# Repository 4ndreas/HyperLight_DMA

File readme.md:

# Hyperlight LED Driver
STM32F407 based WS2811/12 Led driver with 16-channel DMA output

## variant 
* added custom variant with DMA interrupt function

## patched libraies are
* Artnet
* Ethernet
	* Changed SPI speed
	* Port so 2 with increases the buffer in the W5500 chip per port to 8k
* Adafruit_SSD1306
	* Display size to 128x64
	
* Overrides for ST SPI Hal Code beed as compile options: -include "<absolute-src-path>/make_weak.h"

## ToDo

* Improvement for
    * better bit sorting
    * setLED function
    * setSnakeLED
    * better solution for other color modes

* Webserver Config for
    * Color Mode
    * offset 
    * Snake Wireing
    * FPS Counter

* USB test
* SD-Card 
* better Webserver with SD card or the website.h methode
* DMX out

## How to Install

```
https://github.com/stm32duino/BoardManagerFiles/raw/master/STM32/package_stm_index.json
```

![alt text][preferences1]
![alt text][preferences2]

### Adding a new board variant 

Path to the boards:

coppy the variants\Hyperlight folder in the package dir:

```
\Sloeber\arduinoPlugin\packages\STM32\hardware\stm32\1.7.0\variants\Hyperlight
```
or if the plain arduino IDE is used in  
```
.user\AppData\Local\Arduino15\packages\STM32\hardware\stm32\1.7.0\variants
```

Setting for the board:

Optimize: "Smallest(-Os default)"

![alt text][properties]

Add make_weak to "compiler Options"
```
-include "C:\Users\ahoel\Documents\sloeber-workspace\hyperlight_dma\make_weak.h"
```
![alt text][properties2]

### How to Debug
See the wiki form the STM32 Core
https://github.com/stm32duino/wiki/wiki/How-to-debug

Download sloeber-IDE form 
http://eclipse.baeyens.it/index.shtml

Change Target to:
```
-s "${openocd_path}/../scripts" -f interface/stlink-v2-1.cfg -f target/stm32f4x.cfg
```
![alt text][debug1]
![alt text][debug2]

[preferences1]: img/preferences_1.JPG "Settings URL for STM32Core"
[preferences2]: img/preferences_2.JPG "Settings URL for STM32Core"
[properties]: img/properties.JPG "properties of the arduino ide"
[debug1]: img/debug_1.JPG "Settings URL for OCD Debugging"
[debug2]: img/debug_2.JPG "Settings URL for OCD Debugging"

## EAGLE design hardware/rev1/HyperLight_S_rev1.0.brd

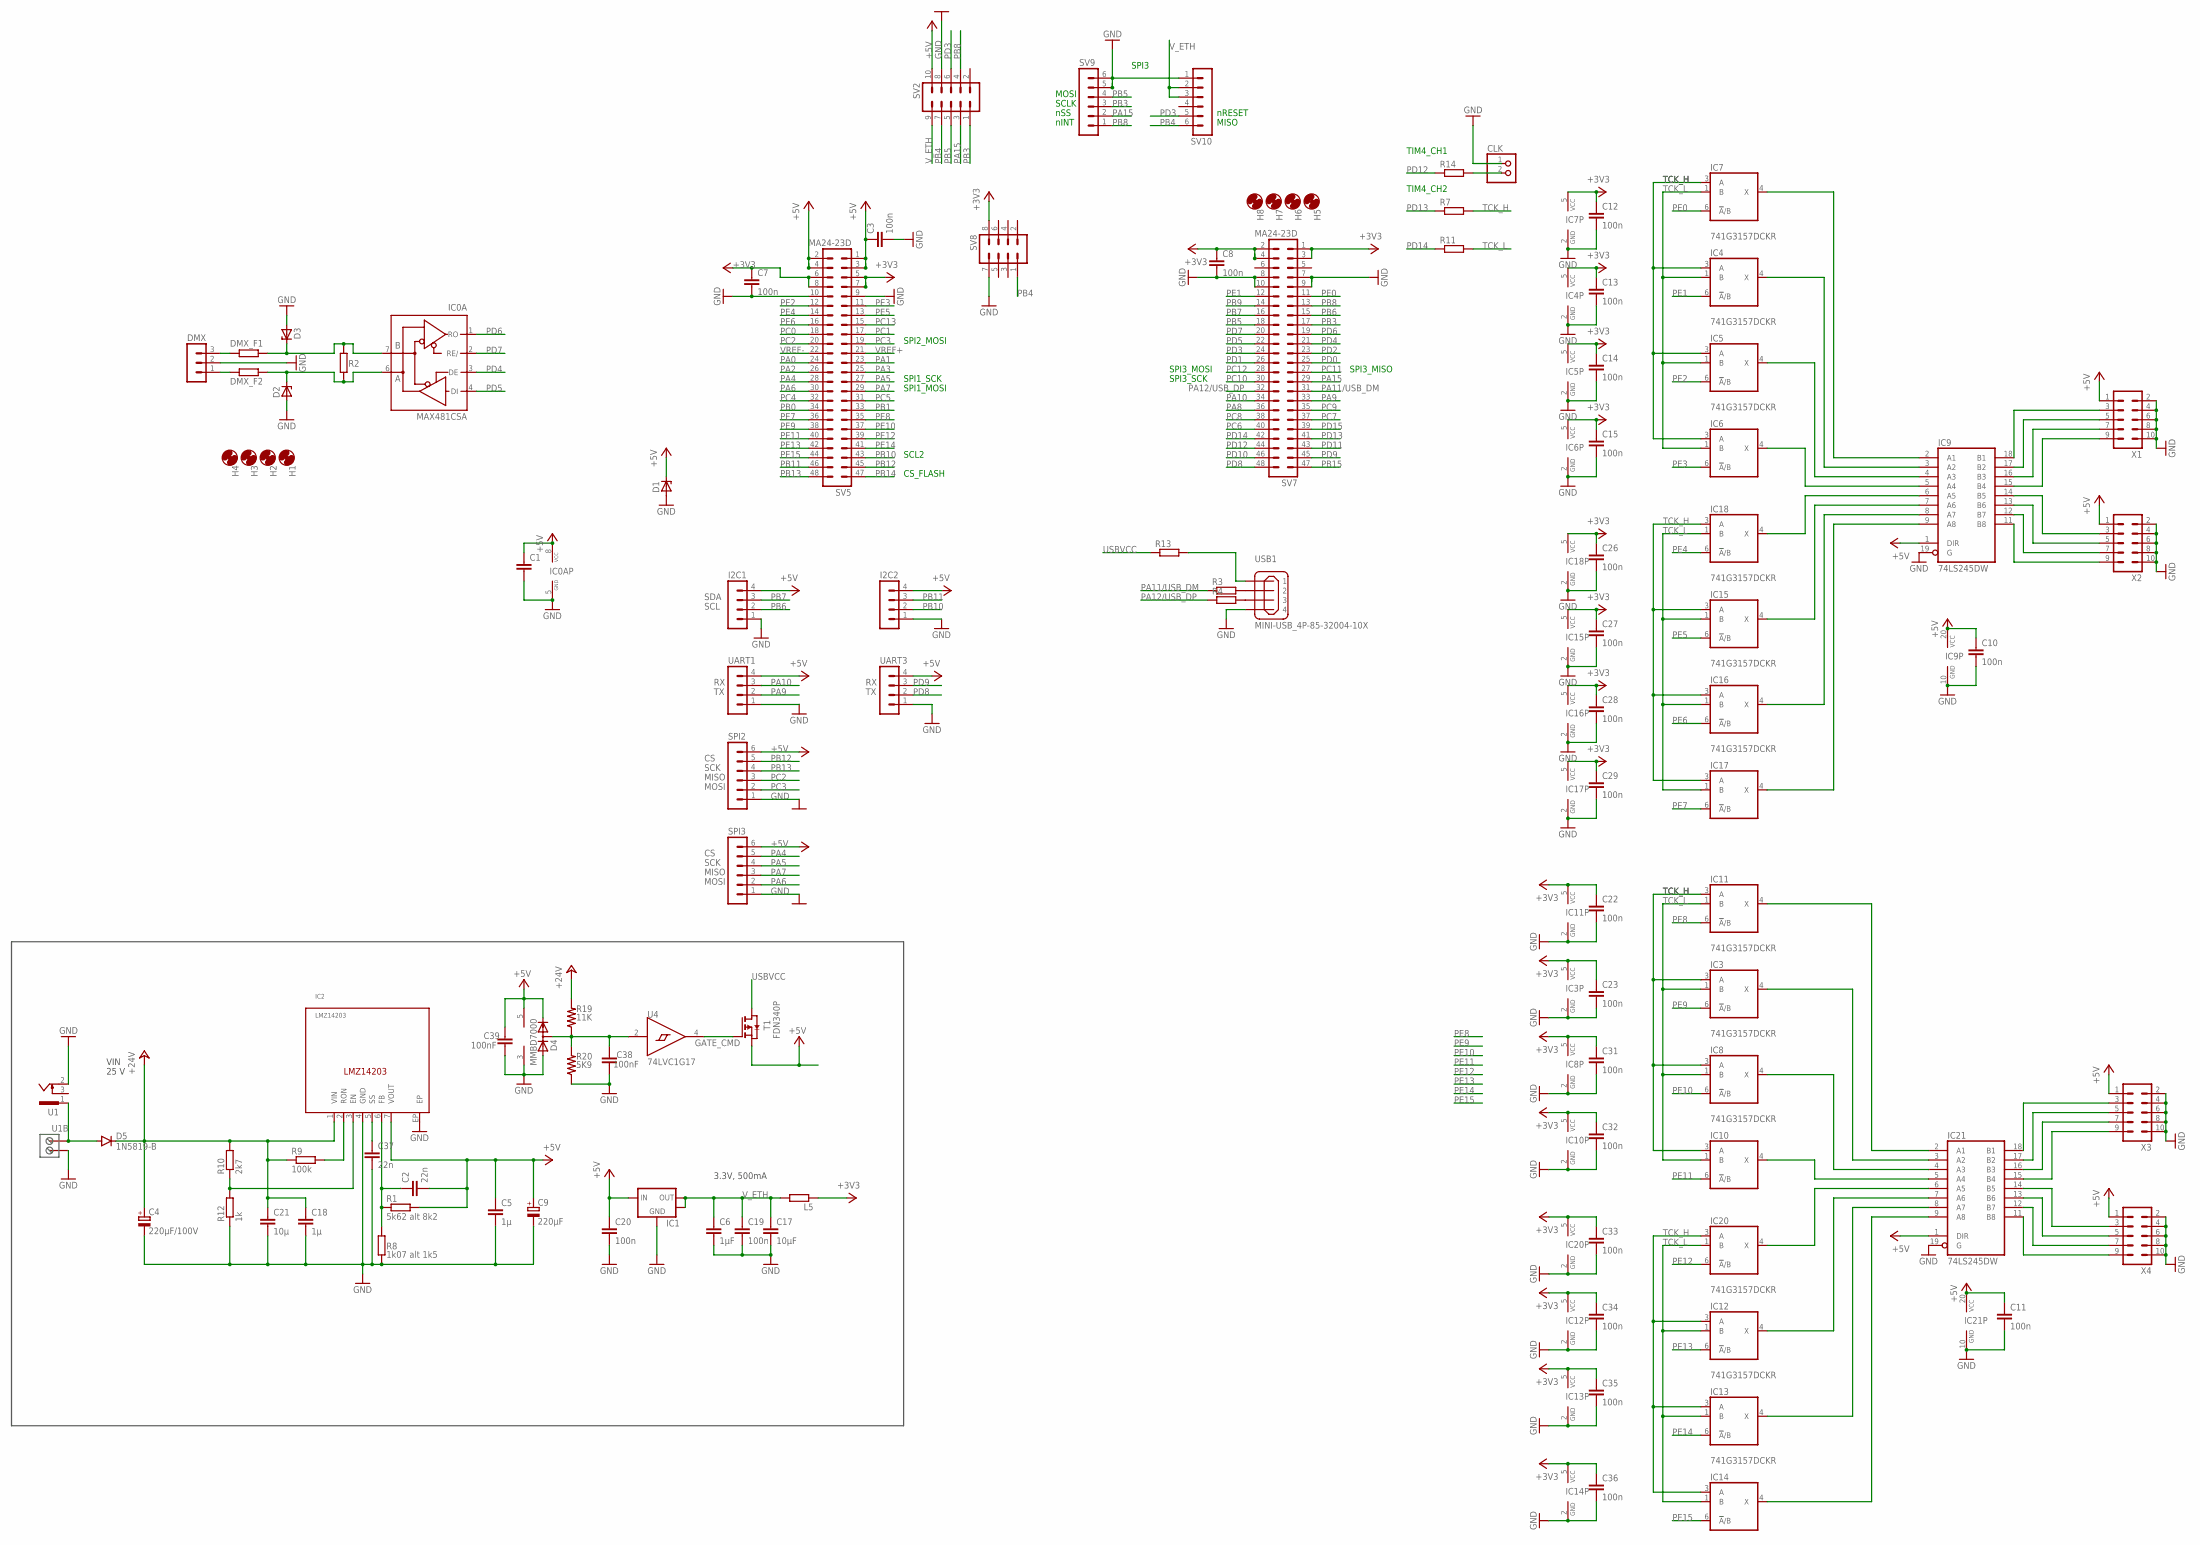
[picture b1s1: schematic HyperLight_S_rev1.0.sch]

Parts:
C1: C-EUC0805; C0805
C2, C37: 22n; C0805
C3, C7, C8, C19, C20: 100n; C0805
C4: 220µF/100V; 153CLV-0810
C5, C18: 1µ; C0805
C6: 1µF; C0805
C9: 220µF; 153CLV-0810
C10, C11, C12, C13, C14, C15, C22, C23, C26, C27, C28, C29, C31, C32, C33, C34, C35, C36: 100n; C0603
C17: 10µF; C0805
C21: 10µ; C0805
C38, C39: 100nF; C0402
CLK: PINHD-1X2; 1X02
D1, D2, D3: ZENER-DIODESMB; SMB
D4: MMBD7000; SC70-3-R
D5: 1N5819-B; SMB
DMX: MA03-1
DMX_F1, DMX_F2: R-EU_R0805; R0805
H1, H2, H3, H4, H5, H6, H7, H8: MOUNT-HOLE3.2; 3,2
I2C1, I2C2: MA04-1
IC0A: MAX481CSA; SO08
IC1: LM1117; SOT223
IC2: LMZ14203; TO-PMOD
IC3, IC4, IC5, IC6, IC7, IC8, IC10, IC11, IC12, IC13, IC14, IC15, IC16, IC17, IC18, IC20: 741G3157DCKR; DCK_R-PDSO-G6
IC9, IC21: 74LS245DW; SO20W
L5: R-EU_R0603; R0603
R1: 5k62 alt 8k2; R0805
R2, R3, R4, R7, R11, R14: R-EU_R0805; R0805
R8: 1k07 alt 1k5; R0805
R9: 100k; R0805
R10: 2k7; R0805
R12: 1k; R0805
R13: R-EU_R1206; R1206
R19: 11K; R0402
R20: 5K9; R0402
SPI2, SPI3: MA06-1
SV2: MA05-2
SV5, SV7: MA24-23D; HDRVR48W64P254_2X24_6096X508X762B
SV8: MA04-2MALE_3D; HDRV8W64P254_2X4_1016X508X838B
SV9, SV10: MA06-1FEMALE_3D; HDRVR6W64P254_1X6_1524X254X762B
T1: FDN340P; SOT-23
U1: 733980-62
U1B: RIACON101-02
U4: 74LVC1G17; SOT-553
UART1, UART3: MA04-1
USB1: MINI-USB_4P-85-32004-10X; 85-32004-10X
X1, X2, X3, X4: MA05-2MA05-2S; MA05-2S

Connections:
+3V3: C7.1, C8.1, C12.1, C13.1, C14.1, C15.1, C22.1, C23.1, C26.1, C27.1, C28.1, C29.1, C31.1, C32.1, C33.1, C34.1, C35.1, C36.1, IC3.5 (VCC), IC4.5 (VCC), IC5.5 (VCC), IC6.5 (VCC), IC7.5 (VCC), IC8.5 (VCC), IC10.5 (VCC), IC11.5 (VCC), IC12.5 (VCC), IC13.5 (VCC), IC14.5 (VCC), IC15.5 (VCC), IC16.5 (VCC), IC17.5 (VCC), IC18.5 (VCC), IC20.5 (VCC), L5.1, SV5.5, SV5.6, SV5.7, SV5.8, SV7.1, SV7.2, SV7.3, SV7.4, SV8.8
+5V: C1.1, C2.2, C3.1, C5.1, C9.+, C10.1, C11.1, C20.1, C39.2, D1.C, D4.2 (C), I2C1.4, I2C2.4, IC0A.8 (VCC), IC1.3 (IN), IC2.7 (VOUT), IC9.1 (DIR), IC9.20 (VCC), IC21.1 (DIR), IC21.20 (VCC), R1.2, SPI2.6, SPI3.6, SV2.10, SV5.1, SV5.2, SV5.3, SV5.4, T1.2 (S), U4.5 (VCC), UART1.4, UART3.4, X1.1, X2.1, X3.1, X4.1
+24V: C4.+, C18.1, C21.1, D5.C, IC2.1 (VIN), R9.1, R10.2, R19.2
CMP: C38.2, D4.3 (AC), R19.1, R20.2, U4.2 (A)
GATE_CMD: T1.3 (G), U4.4 (Y)
GND: C1.2, C3.2, C4.-, C5.2, C6.2, C7.2, C8.2, C9.-, C10.2, C11.2, C12.2, C13.2, C14.2, C15.2, C17.2, C18.2, C19.2, C20.2, C21.2, C22.2, C23.2, C26.2, C27.2, C28.2, C29.2, C31.2, C32.2, C33.2, C34.2, C35.2, C36.2, C37.2, C38.1, C39.1, CLK.1, D1.A, D2.A, D3.A, D4.1 (A), DMX.2, I2C1.1, I2C2.1, IC0A.5 (GND), IC1.1 (GND), IC2.4 (GND), IC2.EP, IC3.2 (GND), IC4.2 (GND), IC5.2 (GND), IC6.2 (GND), IC7.2 (GND), IC8.2 (GND), IC9.10 (GND), IC9.19 (G), IC10.2 (GND), IC11.2 (GND), IC12.2 (GND), IC13.2 (GND), IC14.2 (GND), IC15.2 (GND), IC16.2 (GND), IC17.2 (GND), IC18.2 (GND), IC20.2 (GND), IC21.10 (GND), IC21.19 (G), R8.1, R12.1, R20.1, SPI2.1, SPI3.1, SV2.8, SV5.9, SV5.10, SV7.7, SV7.8, SV7.9, SV7.10, SV8.7, SV9.5, SV9.6, SV10.1, U1.2, U1B.P$2, U4.3 (GND), UART1.1, UART3.1, USB1.4, X1.2, X1.4, X1.6, X1.8, X1.10, X2.2, X2.4, X2.6, X2.8, X2.10, X3.2, X3.4, X3.6, X3.8, X3.10, X4.2, X4.4, X4.6, X4.8, X4.10
unnamed: IC7.4 (X), IC9.2 (A1)
unnamed: IC5.4 (X), IC9.4 (A3)
unnamed: R3.2, USB1.2
unnamed: IC6.4 (X), IC9.5 (A4)
unnamed: IC4.4 (X), IC9.3 (A2)
unnamed: IC9.18 (B1), X1.3
unnamed: D3.C, DMX_F1.1, IC0A.7 (B), R2.2
unnamed: D2.C, DMX_F2.1, IC0A.6 (A), R2.1
unnamed: R4.2, USB1.3
unnamed: C2.1, IC2.6 (FB), R1.1, R8.2
unnamed: IC9.6 (A5), IC18.4 (X)
unnamed: IC2.2 (RON), R9.2
unnamed: IC11.4 (X), IC21.2 (A1)
unnamed: C37.1, IC2.5 (SS)
unnamed: IC9.9 (A8), IC17.4 (X)
unnamed: IC2.3 (EN), R10.1, R12.2
unnamed: D5.A, U1.1, U1B.P$1
unnamed: IC9.8 (A7), IC16.4 (X)
unnamed: IC9.7 (A6), IC15.4 (X)
unnamed: IC9.17 (B2), X1.5
unnamed: IC9.16 (B3), X1.7
unnamed: IC9.15 (B4), X1.9
unnamed: DMX.3, DMX_F1.2
unnamed: DMX.1, DMX_F2.2
unnamed: IC8.4 (X), IC21.4 (A3)
unnamed: IC10.4 (X), IC21.5 (A4)
unnamed: IC20.4 (X), IC21.6 (A5)
unnamed: IC14.4 (X), IC21.9 (A8)
unnamed: IC13.4 (X), IC21.8 (A7)
unnamed: IC12.4 (X), IC21.7 (A6)
unnamed: IC3.4 (X), IC21.3 (A2)
unnamed: R13.2, USB1.1
unnamed: CLK.2, R14.2
unnamed: IC21.18 (B1), X3.3
unnamed: IC21.17 (B2), X3.5
unnamed: IC21.16 (B3), X3.7
unnamed: IC21.15 (B4), X3.9
unnamed: IC21.14 (B5), X4.3
unnamed: IC21.13 (B6), X4.5
unnamed: IC21.12 (B7), X4.7
unnamed: IC21.11 (B8), X4.9
unnamed: IC9.14 (B5), X2.3
unnamed: IC9.13 (B6), X2.5
unnamed: IC9.12 (B7), X2.7
unnamed: IC9.11 (B8), X2.9
PA0: SV5.24
PA1: SV5.23
PA2: SV5.26
PA3: SV5.25
PA4: SPI3.5, SV5.28
PA5: SPI3.4, SV5.27
PA6: SPI3.2, SV5.30
PA7: SPI3.3, SV5.29
PA8: SV7.36
PA9: SV7.33, UART1.2
PA10: SV7.34, UART1.3
PA11/USB_DM: R3.1, SV7.31
PA12/USB_DP: R4.1, SV7.32
PA15: SV2.3, SV7.29, SV9.2
PB0: SV5.34
PB1: SV5.33
PB3: SV2.1, SV7.17, SV9.3
PB4: SV2.7, SV8.1, SV10.6
PB5: SV2.5, SV7.18, SV9.4
PB6: I2C1.2, SV7.15
PB7: I2C1.3, SV7.16
PB8: SV2.4, SV7.13, SV9.1
PB9: SV7.14
PB10: I2C2.2, SV5.43
PB11: I2C2.3, SV5.46
PB12: SPI2.5, SV5.45
PB13: SPI2.4, SV5.48
PB14: SV5.47
PB15: SV7.47
PC0: SV5.18
PC1: SV5.17
PC2: SPI2.3, SV5.20
PC3: SPI2.2, SV5.19
PC4: SV5.32
PC5: SV5.31
PC6: SV7.40
PC7: SV7.37
PC8: SV7.38
PC9: SV7.35
PC10: SV7.30
PC11: SV7.27
PC12: SV7.28
PC13: SV5.15
PD0: SV7.25
PD1: SV7.26
PD2: SV7.23
PD3: SV2.6, SV7.24, SV10.5
PD4: IC0A.3 (DE), SV7.21
PD5: IC0A.4 (DI), SV7.22
PD6: IC0A.1 (RO), SV7.19
PD7: IC0A.2 (RE/), SV7.20
PD8: SV7.48, UART3.2
PD9: SV7.45, UART3.3
PD10: SV7.46
PD11: SV7.43
PD12: R14.1, SV7.44
PD13: R7.1, SV7.41
PD14: R11.1, SV7.42
PD15: SV7.39
PE0: IC7.6 (!A!/B), SV7.11
PE1: IC4.6 (!A!/B), SV7.12
PE2: IC5.6 (!A!/B), SV5.12
PE3: IC6.6 (!A!/B), SV5.11
PE4: IC18.6 (!A!/B), SV5.14
PE5: IC15.6 (!A!/B), SV5.13
PE6: IC16.6 (!A!/B), SV5.16
PE7: IC17.6 (!A!/B), SV5.36
PE8: IC11.6 (!A!/B), SV5.35
PE9: IC3.6 (!A!/B), SV5.38
PE10: IC8.6 (!A!/B), SV5.37
PE11: IC10.6 (!A!/B), SV5.40
PE12: IC20.6 (!A!/B), SV5.39
PE13: IC12.6 (!A!/B), SV5.42
PE14: IC13.6 (!A!/B), SV5.41
PE15: IC14.6 (!A!/B), SV5.44
TCK_H: IC3.3 (A), IC4.3 (A), IC5.3 (A), IC6.3 (A), IC7.3 (A), IC8.3 (A), IC10.3 (A), IC11.3 (A), IC12.3 (A), IC13.3 (A), IC14.3 (A), IC15.3 (A), IC16.3 (A), IC17.3 (A), IC18.3 (A), IC20.3 (A), R7.2
TCK_L: IC3.1 (B), IC4.1 (B), IC5.1 (B), IC6.1 (B), IC7.1 (B), IC8.1 (B), IC10.1 (B), IC11.1 (B), IC12.1 (B), IC13.1 (B), IC14.1 (B), IC15.1 (B), IC16.1 (B), IC17.1 (B), IC18.1 (B), IC20.1 (B), R11.2
USBVCC: R13.1, T1.1 (D)
VREF+: SV5.21
VREF-: SV5.22
V_ETH: C6.1, C17.1, C19.1, IC1.2 (OUT), IC1.4 (PAD), L5.2, SV2.9, SV10.2, SV10.3

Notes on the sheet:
MOSI
SCLK
nSS
nINT
nRESET
MISO
SPI1_MOSI
SPI1_SCK
SPI3_SCK
SPI3_MOSI
SPI3_MISO
SPI2_MOSI
SCL2
CS_FLASH
SPI3
TIM4_CH1
TIM4_CH2
25 V
VIN
3.3V, 500mA
SDA
SCL
SCK

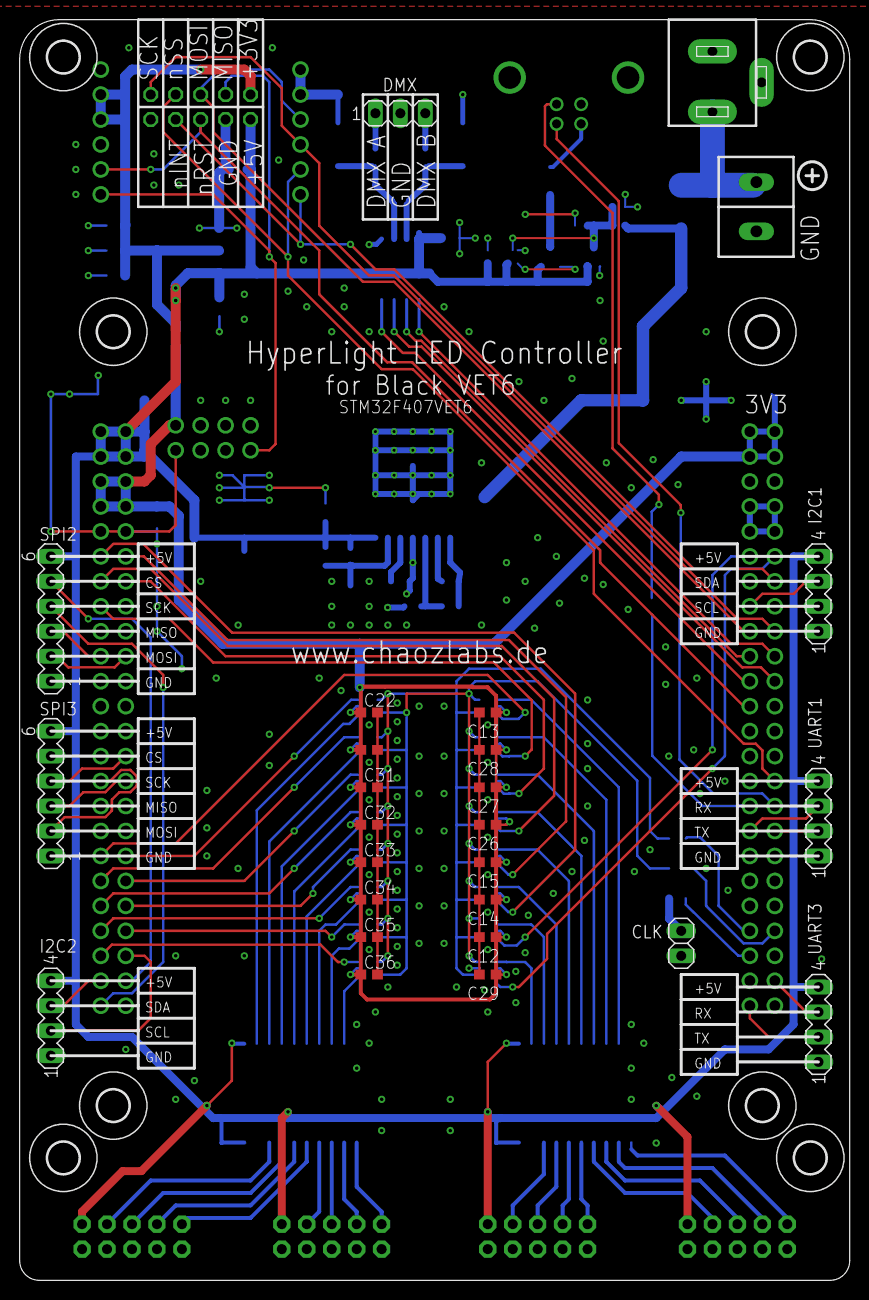
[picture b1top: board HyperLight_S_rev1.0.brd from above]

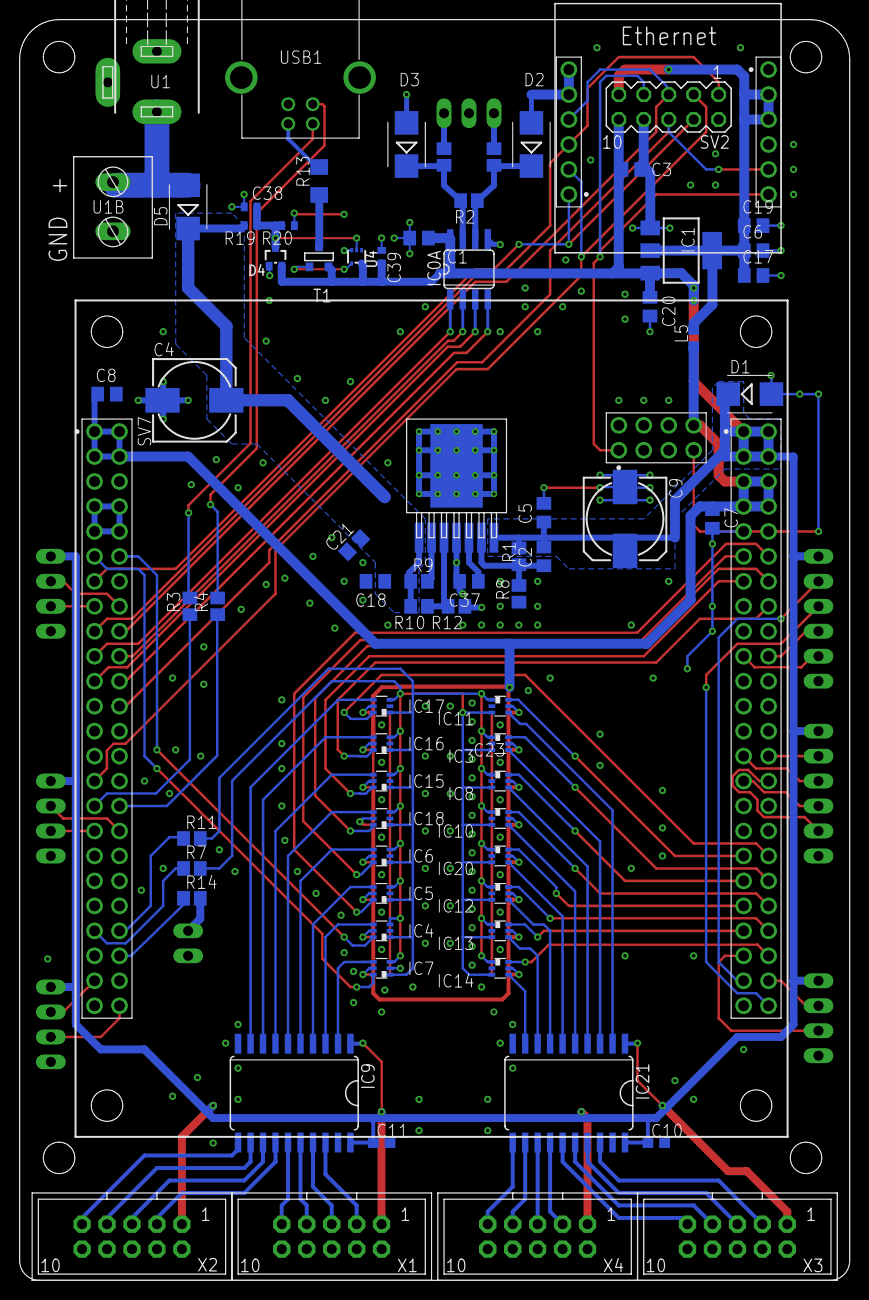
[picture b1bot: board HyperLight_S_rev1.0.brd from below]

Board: 2 copper layers, 84.5 x 128.3 mm, 109 parts (77 on the bottom side), 102 nets.

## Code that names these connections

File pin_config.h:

/*
 * pin_config.h
 *
 *  Created on: 24.11.2019
 *      Author: ahoel
 */

#ifndef PIN_CONFIG_H_
#define PIN_CONFIG_H_




// D1 = Power
#define LED_BUILTIN_D2 PA6  // note LED overlaps with hardware SPI-1 ENC_MISO_PIN
#define LED_BUILTIN_D3 PA7  // note LED overlaps with hardware SPI-1 ENC_MOSI_PIN

// W5500 Ethernet
// HW-SPI-3 or HW_SPI-1
#define ETH_MOSI_PIN  PB5
#define ETH_MISO_PIN  PB4
#define ETH_SCK_PIN   PB3
#define ETH_SCS_PIN   PA15
#define ETH_INT_PIN   PB8
#define ETH_RST_PIN   PD3




/* UART2 To DMX IN/OUT	*/
//#define UART2_TX_PIN  PD5	// TO MAX481 DI	- tx data in
//#define UART2_RX_PIN  PD6	// TO MAX481 RO - rx data out
//#define UART2_DE_PIN  PD7	// TO MAX481 DE - data direction
//#define UART2_RE_PIN  PD4	// TO MAX481 RE - Recieve nEnable
//// for RX RE LOW,  DE LOW
//// for TX RE HIGH, DE HIGH


/* HW-SPI-2 6-Pin Header	*/
/* +5V */
#define SPI2_CS_PIN    PB12
#define SPI2_SCK_PIN   PB13
#define SPI2_MISO_PIN  PC2
#define SPI2_MOSI_PIN  PC3
/* GND */


/* HW-SPI-3 6-Pin Header	*/
/* +5V */
#define SPI3_CS_PIN    PA4
#define SPI3_CLK_PIN   PA5
#define SPI3_MOSI_PIN  PA7
#define SPI3_MISO_PIN  PA6
/* GND */


/* UART1 4-Pin Header	*/
/* +5V */
#define UART1_RX_PIN  PA10
#define UART1_TX_PIN  PA9
/* GND */

/* UART3 4-Pin Header	*/
/* +5V */
#define UART3_RX_PIN  PD9
#define UART3_TX_PIN  PD8
/* GND */

/* I2C1 4-Pin Header	*/
/* +5V */
#define I2C1_SDA_PIN  PB7
#define I2C1_SCL_PIN  PB6
/* GND */

/* I2C2 4-Pin Header	*/
/* +5V */
#define I2C2_SDA_PIN  PB11
#define I2C2_SCL_PIN  PB10
/* GND */

/* Onbaord Flash		*/
// W25Q16JV
// https://stm32-base.org/boards/STM32F407VET6-STM32-F4VE-V2.0.html
#define SPI_FLASH_CS	PB0
#define SPI_FLASH_DO	PB4
//#define SPI_FLASH_WP	+3V3
#define SPI_FLASH_DI	PB5
#define SPI_FLASH_CLK	PB3
//#define SPI_FLASH_HOLD +3V3

/* SD-Card Pins  		*/
// to do


/* Override Board SPI mappings so Ethernet is on SPI1 defined as WEAK in board file*/
const PinMap PinMap_SPI_MOSI[] = {
  {PA_7,  SPI1, STM_PIN_DATA(STM_MODE_AF_PP, GPIO_PULLUP, GPIO_AF5_SPI1)},
  {PB_5,  SPI1, STM_PIN_DATA(STM_MODE_AF_PP, GPIO_PULLUP, GPIO_AF5_SPI1)},
  {PB_5,  SPI3, STM_PIN_DATA(STM_MODE_AF_PP, GPIO_PULLUP, GPIO_AF6_SPI3)},
  {PB_15, SPI2, STM_PIN_DATA(STM_MODE_AF_PP, GPIO_PULLUP, GPIO_AF5_SPI2)},
  {PC_3,  SPI2, STM_PIN_DATA(STM_MODE_AF_PP, GPIO_PULLUP, GPIO_AF5_SPI2)},
  {PC_12, SPI3, STM_PIN_DATA(STM_MODE_AF_PP, GPIO_PULLUP, GPIO_AF6_SPI3)},
  {NC,    NP,    0}
};

 const PinMap PinMap_SPI_MISO[] = {
  {PA_6,  SPI1, STM_PIN_DATA(STM_MODE_AF_PP, GPIO_PULLUP, GPIO_AF5_SPI1)},
  {PB_4,  SPI1, STM_PIN_DATA(STM_MODE_AF_PP, GPIO_PULLUP, GPIO_AF5_SPI1)},
  {PB_4,  SPI3, STM_PIN_DATA(STM_MODE_AF_PP, GPIO_PULLUP, GPIO_AF6_SPI3)},
  {PB_14, SPI2, STM_PIN_DATA(STM_MODE_AF_PP, GPIO_PULLUP, GPIO_AF5_SPI2)},
  {PC_2,  SPI2, STM_PIN_DATA(STM_MODE_AF_PP, GPIO_PULLUP, GPIO_AF5_SPI2)},
  {PC_11, SPI3, STM_PIN_DATA(STM_MODE_AF_PP, GPIO_PULLUP, GPIO_AF6_SPI3)},
  {NC,    NP,    0}
};

const PinMap PinMap_SPI_SCLK[] = {
  {PA_5,  SPI1, STM_PIN_DATA(STM_MODE_AF_PP, GPIO_PULLUP, GPIO_AF5_SPI1)},
  {PB_3,  SPI1, STM_PIN_DATA(STM_MODE_AF_PP, GPIO_PULLUP, GPIO_AF5_SPI1)},
  {PB_3,  SPI3, STM_PIN_DATA(STM_MODE_AF_PP, GPIO_PULLUP, GPIO_AF6_SPI3)},
  {PB_10, SPI2, STM_PIN_DATA(STM_MODE_AF_PP, GPIO_PULLUP, GPIO_AF5_SPI2)},
  {PB_13, SPI2, STM_PIN_DATA(STM_MODE_AF_PP, GPIO_PULLUP, GPIO_AF5_SPI2)},
  {PC_10, SPI3, STM_PIN_DATA(STM_MODE_AF_PP, GPIO_PULLUP, GPIO_AF6_SPI3)},
  {NC,    NP,    0}
};


const PinMap PinMap_SPI_SSEL[] = {
  {PA_4,  SPI1, STM_PIN_DATA(STM_MODE_AF_PP, GPIO_PULLUP, GPIO_AF5_SPI1)},
  //  {PA_4,  SPI3, STM_PIN_DATA(STM_MODE_AF_PP, GPIO_PULLUP, GPIO_AF6_SPI3)},
  {PA_15, SPI1, STM_PIN_DATA(STM_MODE_AF_PP, GPIO_PULLUP, GPIO_AF5_SPI1)},
  {PA_15, SPI3, STM_PIN_DATA(STM_MODE_AF_PP, GPIO_PULLUP, GPIO_AF6_SPI3)},
  {PB_9,  SPI2, STM_PIN_DATA(STM_MODE_AF_PP, GPIO_PULLUP, GPIO_AF5_SPI2)},
  {PB_12, SPI2, STM_PIN_DATA(STM_MODE_AF_PP, GPIO_PULLUP, GPIO_AF5_SPI2)},
  {NC,    NP,    0}
};


#endif /* PIN_CONFIG_H_ */

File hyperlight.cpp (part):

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                          |GPIO_PIN_10|GPIO_PIN_11|GPIO_PIN_12|GPIO_PIN_13
                          |GPIO_PIN_14|GPIO_PIN_15|GPIO_PIN_0|GPIO_PIN_1, GPIO_PIN_RESET);

  /*Configure GPIO pins : PE2 PE3 PE4 PE5
                           PE6 PE7 PE8 PE9
                           PE10 PE11 PE12 PE13
                           PE14 PE15 PE0 PE1 */
  GPIO_InitStruct.Pin = GPIO_PIN_2|GPIO_PIN_3|GPIO_PIN_4|GPIO_PIN_5
                          |GPIO_PIN_6|GPIO_PIN_7|GPIO_PIN_8|GPIO_PIN_9
                          |GPIO_PIN_10|GPIO_PIN_11|GPIO_PIN_12|GPIO_PIN_13
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  GPIO_InitStruct.Speed = GPIO_SPEED_FREQ_LOW;
  HAL_GPIO_Init(GPIOE, &GPIO_InitStruct);

  /*Configure GPIO pins : PD12 PD13 PD14 */
  GPIO_InitStruct.Pin = GPIO_PIN_12|GPIO_PIN_13|GPIO_PIN_14;
  GPIO_InitStruct.Mode = GPIO_MODE_ANALOG;
  GPIO_InitStruct.Pull = GPIO_NOPULL;
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
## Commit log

2019-11-18 init
2019-11-18 dma scheint zu funktionieren
2019-11-18 artnet working
2019-11-19 small changes
2019-11-20 funktioniert soweit
2019-11-22 oled und webserver working
2019-11-24 gitignore
2019-11-24 alles läuft
2019-11-24 ka warum das noch da ist
2019-11-24 pin_config.h und readme.md
2019-11-24 rm release
2019-11-24 gitignore fix
2019-11-24 Gitignore issue fixed
2019-11-24 readme and libraries added
2019-11-24 img added to readme
2019-11-24 removed old not longer needed files
2019-11-24 Added Hardware
2019-11-24 Hardware Serial Debug
2020-11-29 added Pin Config file and other improvements
2020-12-04 added GFX library
2020-12-23 added SPI override to map Ethernet on SPI1 instead of SPI3 since SPI1 is able to 42MBit/s and SPI3 only 22MBit/s
2020-12-29 added STM32F407.svd file for debug
2020-12-29 copy artnet data directly to per universe buffers
2020-12-29 added check if dma is idle
2020-12-29 smarter updater behaviour
2020-12-29 avoid delay in loop
2020-12-30 to do list
2021-01-02 add support for artsync and seq based frame loss detection
2021-01-02 fast and more flexible code for setStripLED
2021-01-02 use artsync to update if possible, also some profiling code
2021-01-11 add spi hal code override
2022-05-06 DMA DMX output first working version
2022-05-06 DMX: double buffering and smarter update behavior
2022-05-06 fix compiler errors
2022-06-16 added config parameter to enable/disable offset led status
2022-06-16 status leds are working now
2022-06-16 removed unused old code
